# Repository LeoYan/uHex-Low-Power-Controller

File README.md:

uHex is the low-power controller which is compatible with Arduino. It is very suitable for the battery power supply environment. 

*Hardware: eagle files: uHexV1_pub.brd, uHexV1_pub.sch

*bootloader:optiboot_atmega328_RC_8MHz.hex

*Arduino board type file:  boards.txt;  In Arduino IDE you can also use "Arduino Pro or Pro Mini (3.3V, 8 MHz) w/ ATmega328" , but the bootloader is different.

*Arduino library: https://github.com/LeoYan/ArduinoLib/tree/master/microPoly

I have authorized DFRobot to production and sale ¦ÌHex.  You can get it at http://www.dfrobot.com/index.php?route=product/product&product_id=1266&search=uHex&description=true

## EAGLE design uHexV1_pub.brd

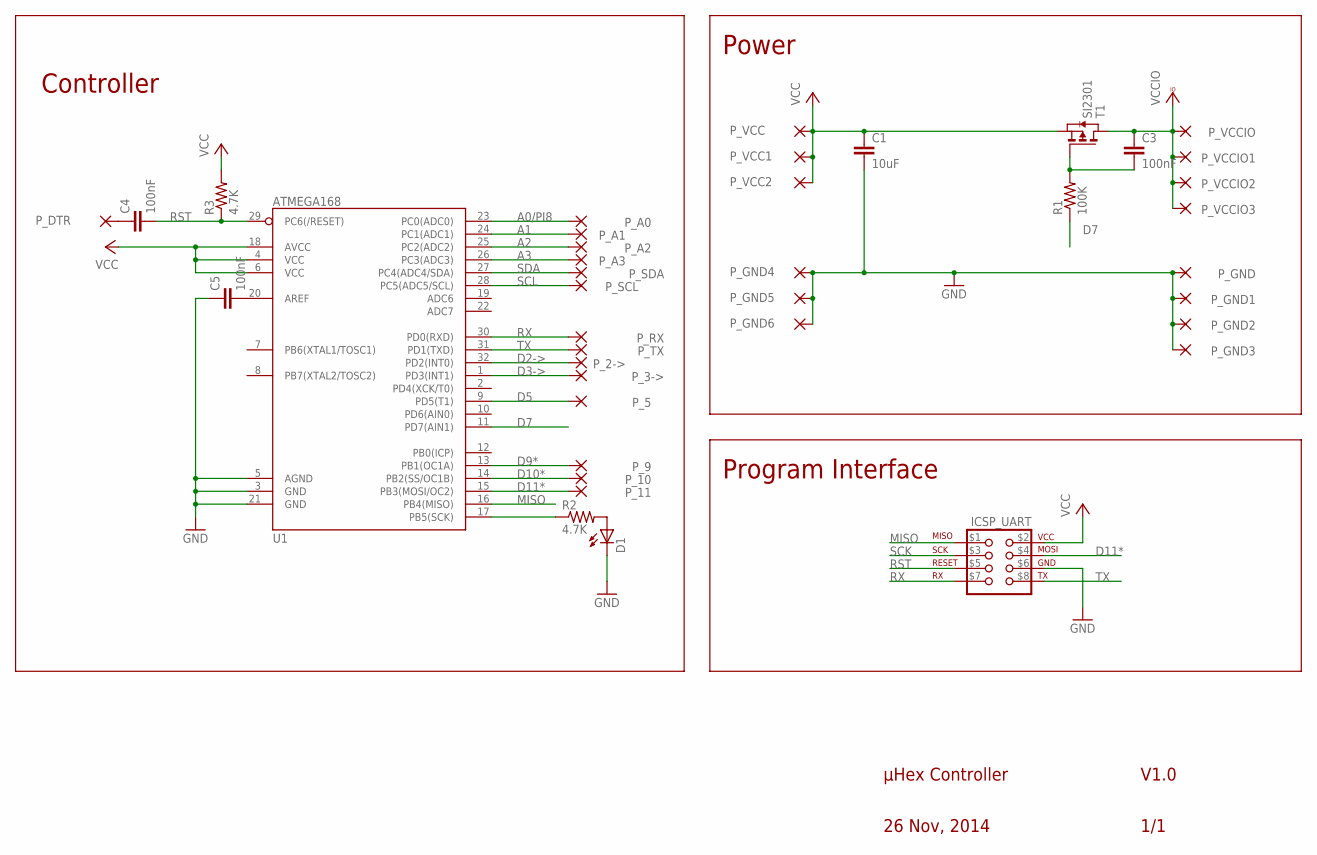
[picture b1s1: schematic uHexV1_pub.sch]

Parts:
C1: 10uF; C0603K
C3, C4, C5: 100nF; C0603K
D1: LED-YELLOW0603; LED-0603
ICSP_UART: ICSP_UART_CONNICSP_UAST_HOLE; ICSP_UART_CONN_HOLE
P_2->, P_3->, P_9, P_10: TH-PAD2.54M01_TH_OFFSET; TH_PAD_OFFSET
P_5, P_11: TH-PAD2.54M01_TH_HORN; TH_PAD_HORN
P_A0, P_A3: TH-PAD2.54M01_TH_HORN; TH_PAD_HORN
P_A1, P_A2: TH-PAD2.54M01_TH_OFFSET; TH_PAD_OFFSET
P_DTR: TH-PAD2.54MO1_TH_DTR; TH_PAD_DTR
P_GND: TH-PAD2.54M01_TH_PWR; TH_PAD_PWR
P_GND1, P_GND2, P_GND3, P_GND4, P_GND5, P_GND6: TH-PAD2.54OFFSET; TH_PAD_PWR_OFFSET
P_RX: TH-PAD2.54M01_TH_OFFSET; TH_PAD_OFFSET
P_SCL: TH-PAD2.54M01_TH_OFFSET; TH_PAD_OFFSET
P_SDA: TH-PAD2.54M01_TH_OFFSET; TH_PAD_OFFSET
P_TX: TH-PAD2.54M01_TH_OFFSET; TH_PAD_OFFSET
P_VCC, P_VCC2: TH-PAD2.54OFFSET; TH_PAD_PWR_OFFSET
P_VCC1: TH-PAD2.54M01_TH_PWR; TH_PAD_PWR
P_VCCIO, P_VCCIO1, P_VCCIO2, P_VCCIO3: TH-PAD2.54OFFSET; TH_PAD_PWR_OFFSET
R1: 100K; 0603-RES
R2, R3: 4.7K; 0603-RES
T1: SI2301; SOT-23
U1: ATMEGA168; TQFP32-08

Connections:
A0/PI8: P_A0.1, U1.23 (PC0(ADC0))
A1: P_A1.P$1, U1.24 (PC1(ADC1))
A2: P_A2.P$1, U1.25 (PC2(ADC2))
A3: P_A3.1, U1.26 (PC3(ADC3))
D2->: P_2->.P$1, U1.32 (PD2(INT0))
D3->: P_3->.P$1, U1.1 (PD3(INT1))
D5: P_5.1, U1.9 (PD5(T1))
D7: R1.1, U1.11 (PD7(AIN1))
D9*: P_9.P$1, U1.13 (PB1(OC1A))
D10*: P_10.P$1, U1.14 (PB2(SS/OC1B))
D11*: ICSP_UART.$4 (4), P_11.1, U1.15 (PB3(MOSI/OC2))
GND: C1.2, C5.1, D1.C, ICSP_UART.$6 (6), P_GND.P$1, P_GND1.P$1, P_GND2.P$1, P_GND3.P$1, P_GND4.P$1, P_GND5.P$1, P_GND6.P$1, U1.3 (GND), U1.5 (AGND), U1.21 (GND)
MISO: ICSP_UART.$1 (1), U1.16 (PB4(MISO))
unnamed: D1.A, R2.2
unnamed: C3.2, R1.2, T1.3 (G)
unnamed: C4.1, P_DTR.1
unnamed: C5.2, U1.20 (AREF)
RST: C4.2, ICSP_UART.$5 (5), R3.1, U1.29 (PC6(/RESET))
RX: ICSP_UART.$7 (7), P_RX.P$1, U1.30 (PD0(RXD))
SCK: ICSP_UART.$3 (3), R2.1, U1.17 (PB5(SCK))
SCL: P_SCL.P$1, U1.28 (PC5(ADC5/SCL))
SDA: P_SDA.P$1, U1.27 (PC4(ADC4/SDA))
TX: ICSP_UART.$8 (8), P_TX.P$1, U1.31 (PD1(TXD))
VCC: C1.1, ICSP_UART.$2 (2), P_VCC.P$1, P_VCC1.P$1, P_VCC2.P$1, R3.2, T1.2 (S), U1.4 (VCC), U1.6 (VCC), U1.18 (AVCC)
VCCIO: C3.1, P_VCCIO.P$1, P_VCCIO1.P$1, P_VCCIO2.P$1, P_VCCIO3.P$1, T1.1 (D)

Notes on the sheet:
Controller
Power
Program Interface
μHex Controller
26 Nov, 2014
V1.0
1/1

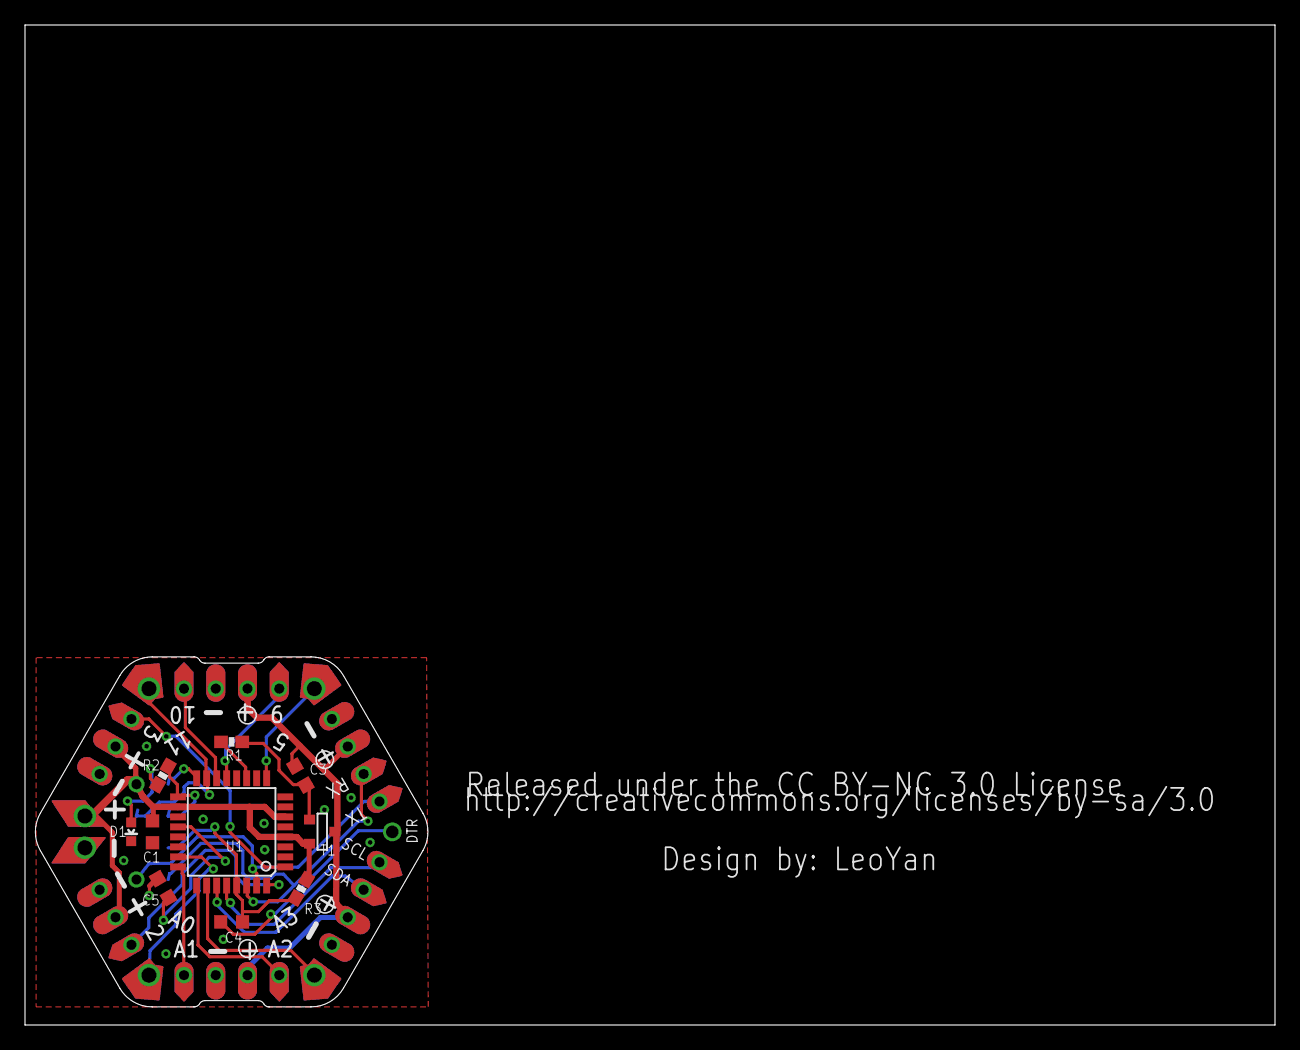
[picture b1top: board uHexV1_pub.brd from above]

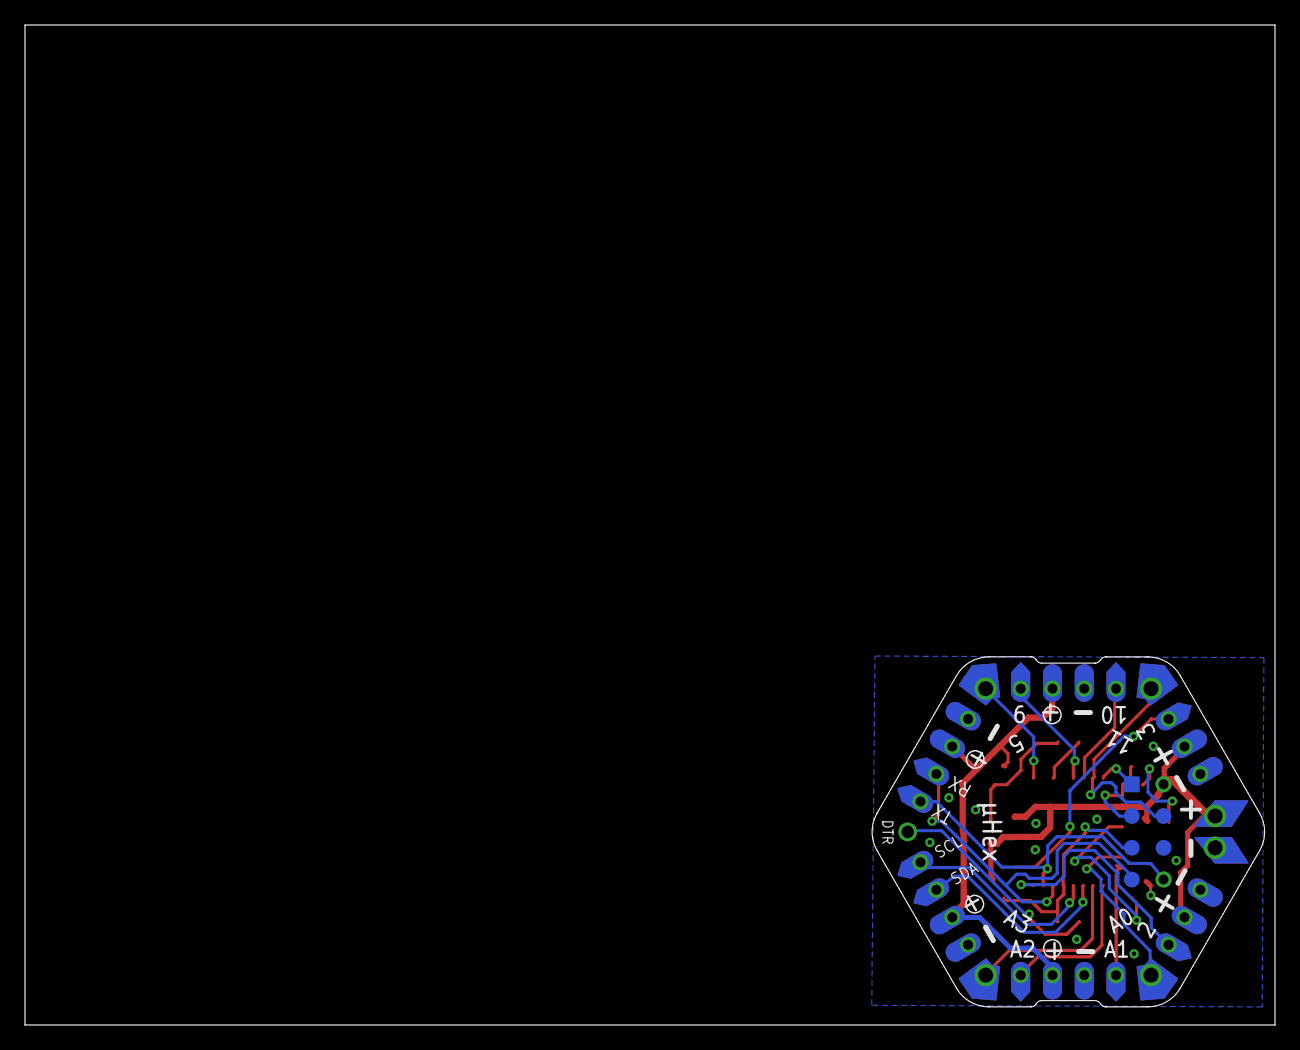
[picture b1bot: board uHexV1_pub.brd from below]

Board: 2 copper layers, 100.0 x 80.0 mm, 40 parts (2 on the bottom side), 25 nets.

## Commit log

2015-04-21 V1.0

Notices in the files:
uHexV1_pub.brd:
Released under the CC BY-NC 3.0 License
http://creativecommons.org/licenses/by-sa/3.0
parts and their libraries:
SparkFun-DigitalIC: Licensing: CC v3.0 Share-Alike You are welcome to use this library for commercial purposes.
